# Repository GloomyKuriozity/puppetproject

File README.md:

# puppetproject
Hub for all puppet project files
ROS2 Jazzy middleware
Raspberry Pi 5/Arduino ATMega2560

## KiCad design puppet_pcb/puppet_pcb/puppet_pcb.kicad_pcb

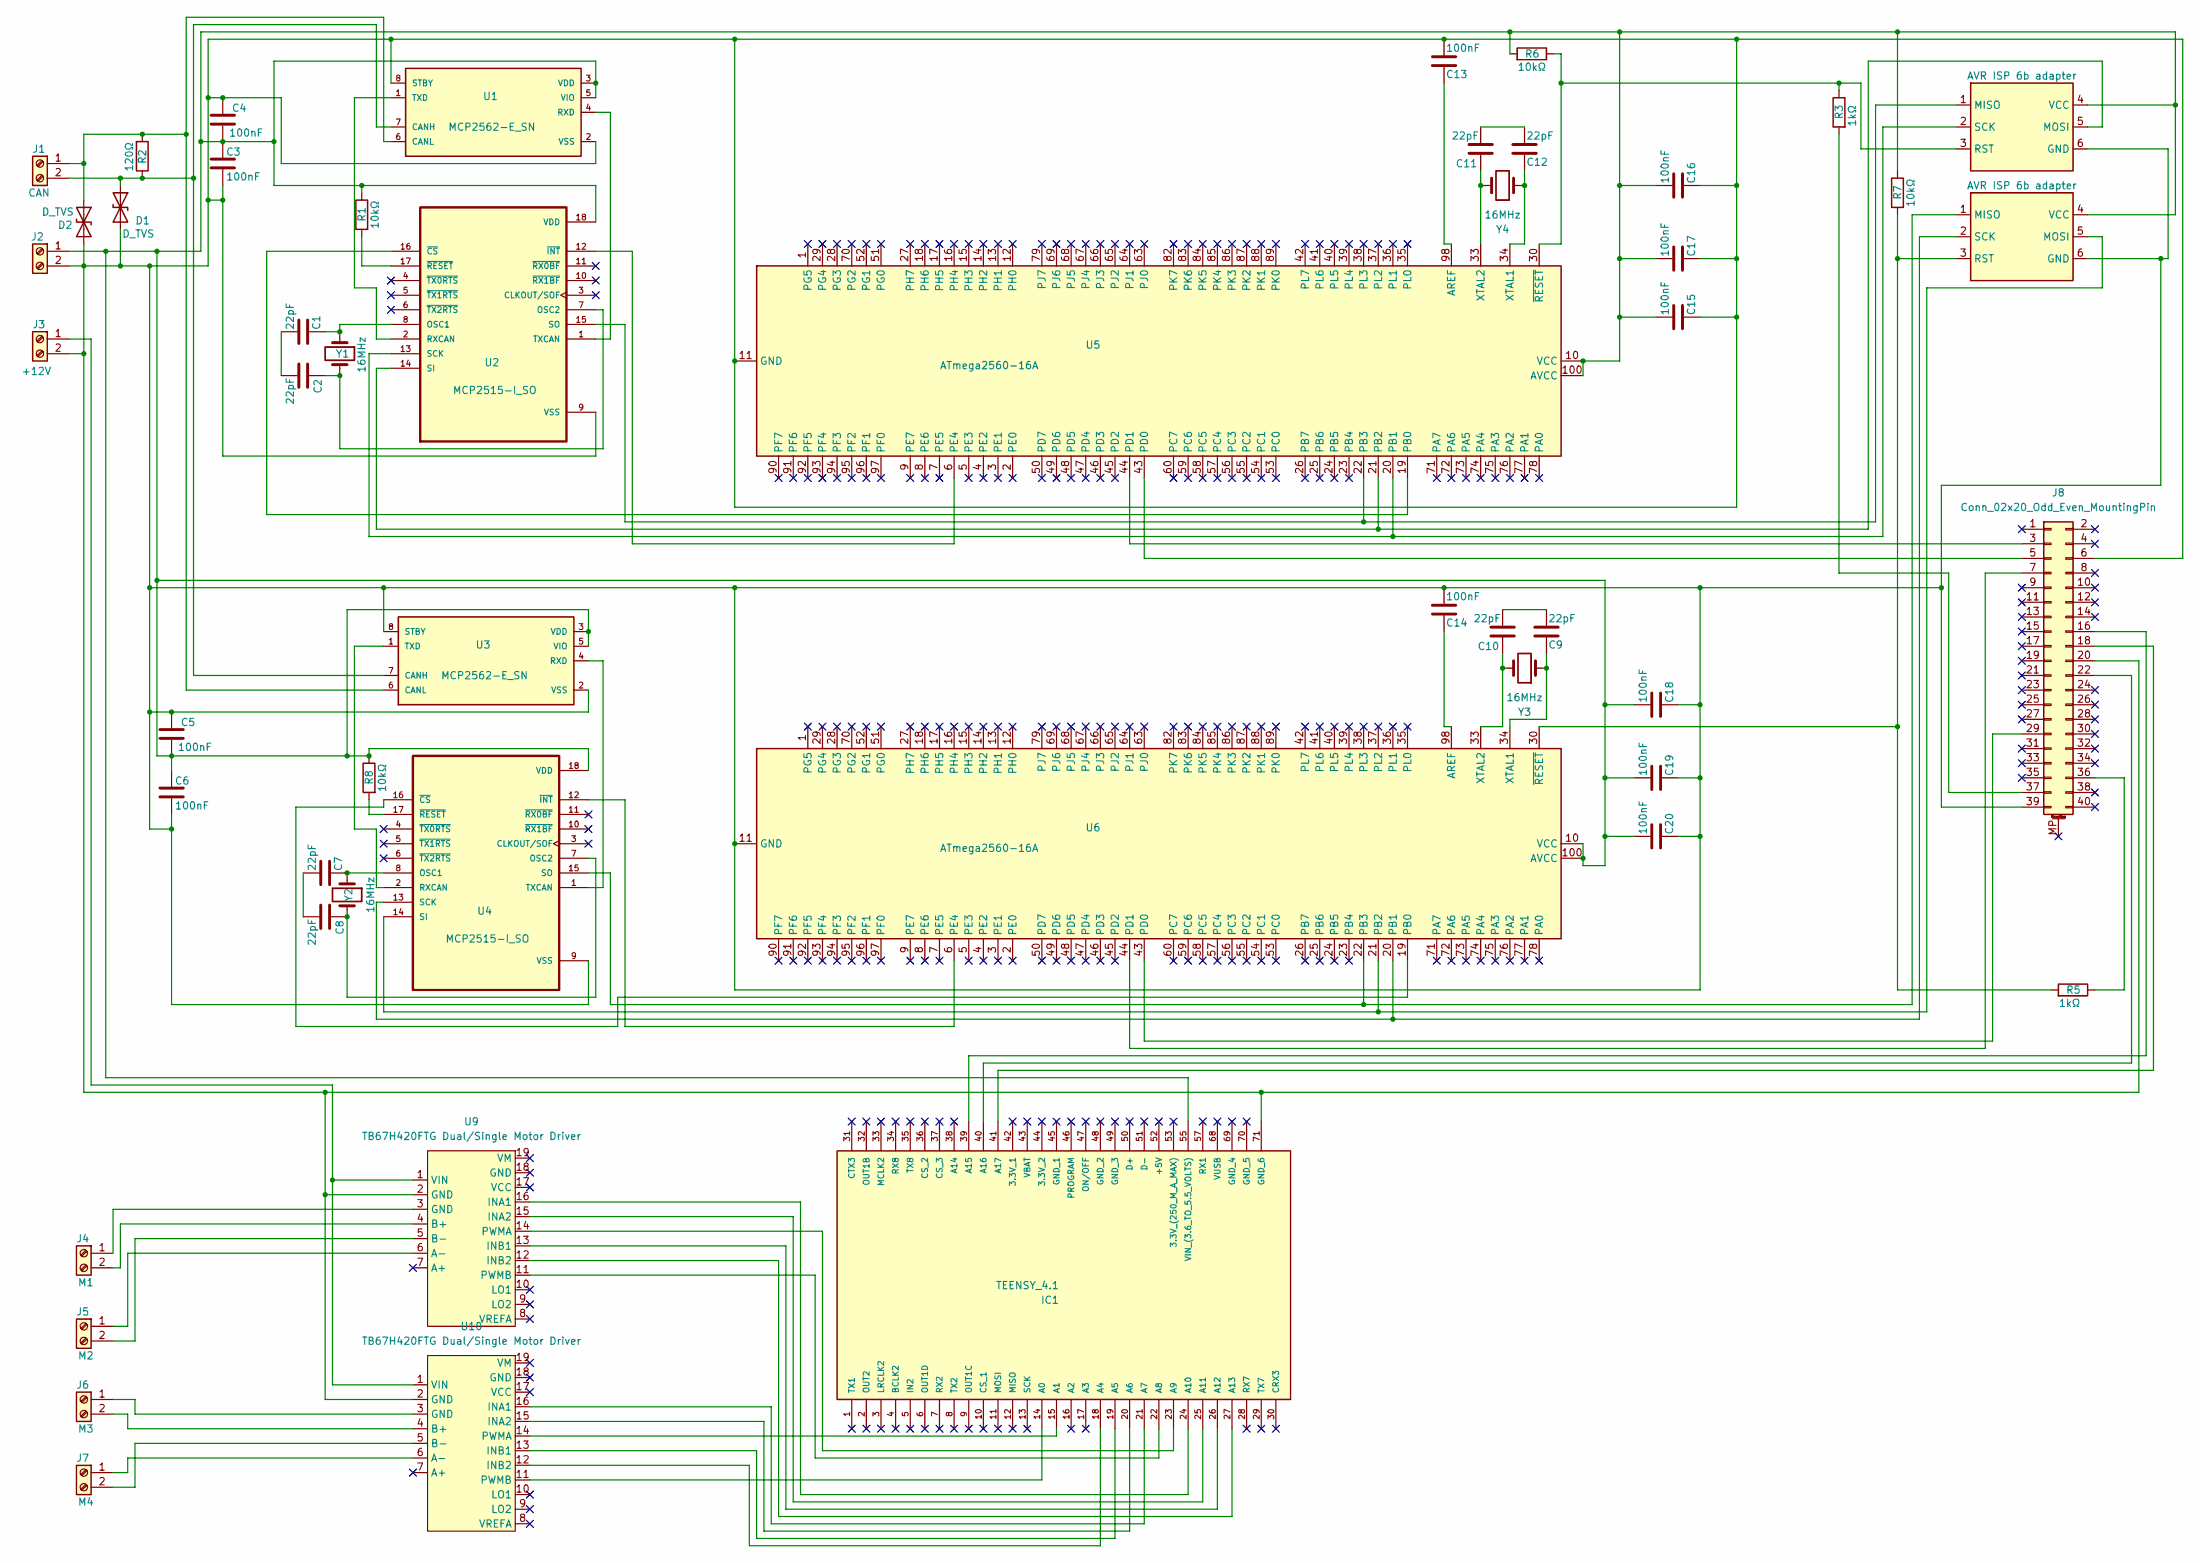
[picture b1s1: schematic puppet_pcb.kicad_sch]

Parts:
C1, C2, C7, C8, C9, C10, C11, C12: 22pF; C_0805_2012Metric
C3, C4, C5, C6, C13, C14, C15, C16, C17, C18, C19, C20: 100nF; C_0805_2012Metric
D1, D2: D_TVS; Nexperia_DSN0603-2_0.6x0.3mm_P0.4mm
IC1: TEENSY_4.1; Manufacturer_Part_Number TEENSY 4.1
J1: CAN; TerminalBlock_MaiXu_MX126-5.0-02P_1x02_P5.00mm
J2: +5V; TerminalBlock_MaiXu_MX126-5.0-02P_1x02_P5.00mm
J3: +12V; TerminalBlock_MaiXu_MX126-5.0-02P_1x02_P5.00mm
J4: M1; TerminalBlock_MaiXu_MX126-5.0-02P_1x02_P5.00mm
J5: M2; TerminalBlock_MaiXu_MX126-5.0-02P_1x02_P5.00mm
J6: M3; TerminalBlock_MaiXu_MX126-5.0-02P_1x02_P5.00mm
J7: M4; TerminalBlock_MaiXu_MX126-5.0-02P_1x02_P5.00mm
J8: Conn_02x20_Odd_Even_MountingPin; IDC-Header_2x20_P2.54mm_Vertical
R1, R6, R7, R8: 10kΩ; R_0805_2012Metric
R2: 120Ω; R_0805_2012Metric
R3, R5: 1kΩ; R_0805_2012Metric
U1, U3: MCP2562-E_SN
U2, U4: MCP2515-I_SO
U5, U6: ATmega2560-16A; TQFP-100_14x14mm_P0.5mm
U7, U8: AVR ISP 6b adapter; Adafruit 6_isp avr adapter
U9, U10: TB67H420FTG Dual/Single Motor Driver; TB67H420FTG Dual_Single Motor
Y1, Y2, Y3, Y4: 16MHz; perçant_quartz

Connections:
unnamed: C1.2, C2.2
unnamed: C7.2, C8.2
unnamed: C9.2, C10.2
unnamed: C11.2, C12.2
unnamed: D1.1 (A1), J1.2, R2.1, U1.7 (CANH), U3.7 (CANH)
unnamed: C3.2, C4.1, C5.1, C6.2, C13.2, C14.2, C15.1, C16.1, C17.1, C18.1, C19.1, C20.1, D1.2 (A2), D2.2 (A2), IC1.71 (GND_6), J2.2, J3.2, J8.6, J8.20, J8.39, U1.2 (VSS), U1.8 (STBY), U2.9 (VSS), U3.2 (VSS), U3.8 (STBY), U4.9 (VSS), U5.11 (GND), U5.32 (GND), U5.62 (GND), U5.81 (GND), U5.99 (GND), U6.11 (GND), U6.32 (GND), U6.62 (GND), U6.81 (GND), U6.99 (GND), U7.6 (GND), U8.6 (GND), U9.2 (GND), U10.2 (GND)
unnamed: D2.1 (A1), J1.1, R2.2, U1.6 (CANL), U3.6 (CANL)
unnamed: IC1.14 (A0), U10.11 (PWMB)
unnamed: IC1.15 (A1), U10.14 (PWMA)
unnamed: IC1.18 (A4), U10.12 (INB2)
unnamed: IC1.19 (A5), U10.13 (INB1)
unnamed: IC1.20 (A6), U10.15 (INA2)
unnamed: IC1.21 (A7), U10.16 (INA1)
unnamed: IC1.22 (A8), U9.11 (PWMB)
unnamed: IC1.23 (A9), U9.14 (PWMA)
unnamed: IC1.24 (A10), U9.16 (INA1)
unnamed: IC1.25 (A11), U9.15 (INA2)
unnamed: IC1.26 (A12), U9.13 (INB1)
unnamed: IC1.27 (A13), U9.12 (INB2)
unnamed: IC1.39 (A15), J8.16
unnamed: IC1.40 (A16), J8.22
unnamed: IC1.41 (A17), J8.18
unnamed: C3.1, C4.2, C5.2, C6.1, C15.2, C16.2, C17.2, C18.2, C19.2, C20.2, IC1.55 (VIN_(3.6_TO_5.5_VOLTS)), J2.1, R1.1, R6.2, R7.1, R8.1, U1.3 (VDD), U1.5 (VIO), U2.18 (VDD), U3.3 (VDD), U3.5 (VIO), U4.18 (VDD), U5.10 (VCC), U5.31 (VCC), U5.61 (VCC), U5.80 (VCC), U5.100 (AVCC), U6.10 (VCC), U6.31 (VCC), U6.61 (VCC), U6.80 (VCC), U6.100 (AVCC), U7.4 (VCC), U8.4 (VCC)
unnamed: J3.1, U9.1 (VIN), U10.1 (VIN)
unnamed: J4.1, U9.3 (GND)
unnamed: J4.2, U9.4 (B+)
unnamed: J5.1, U9.6 (A-)
unnamed: J5.2, U9.5 (B-)
unnamed: J6.1, U10.3 (GND)
unnamed: J6.2, U10.4 (B+)
unnamed: J7.1, U10.6 (A-)
unnamed: J7.2, U10.5 (B-)
unnamed: J8.3, U5.44 (PD1)
unnamed: J8.5, U5.43 (PD0)
unnamed: J8.7, U6.44 (PD1)
unnamed: J8.29, U6.43 (PD0)
unnamed: J8.36, R5.1
unnamed: J8.37, R3.2
unnamed: U1.4 (RXD), U2.1 (TXCAN)
unnamed: U1.1 (TXD), U2.2 (RXCAN)
unnamed: C1.1, U2.8 (OSC1), Y1.1
unnamed: C2.1, U2.7 (OSC2), Y1.2
unnamed: U2.13 (SCK), U5.20 (PB1), U7.2 (SCK)
unnamed: U2.14 (SI), U5.21 (PB2), U7.5 (MOSI)
unnamed: U2.15 (SO), U5.22 (PB3), U7.1 (MISO)
unnamed: U2.16 (~CS), U5.19 (PB0)
unnamed: U2.12 (~INT), U5.6 (PE4)
unnamed: R1.2, U2.17 (~RESET)
unnamed: U3.4 (RXD), U4.1 (TXCAN)
unnamed: U3.1 (TXD), U4.2 (RXCAN)
unnamed: C7.1, U4.8 (OSC1), Y2.1
unnamed: C8.1, U4.7 (OSC2), Y2.2
unnamed: U4.13 (SCK), U6.20 (PB1), U8.2 (SCK)
unnamed: U4.14 (SI), U6.21 (PB2), U8.5 (MOSI)
unnamed: U4.15 (SO), U6.22 (PB3), U8.1 (MISO)
unnamed: U4.16 (~CS), U6.19 (PB0)
unnamed: U4.12 (~INT), U6.6 (PE4)
unnamed: R8.2, U4.17 (~RESET)
unnamed: C13.1, U5.98 (AREF)
unnamed: C12.1, U5.34 (XTAL1), Y4.1
unnamed: C11.1, U5.33 (XTAL2), Y4.2
unnamed: R3.1, R6.1, U5.30 (~RESET), U7.3 (RST)
unnamed: C14.1, U6.98 (AREF)
unnamed: C9.1, U6.34 (XTAL1), Y3.1
unnamed: C10.1, U6.33 (XTAL2), Y3.2
unnamed: R5.2, R7.2, U6.30 (~RESET), U8.3 (RST)

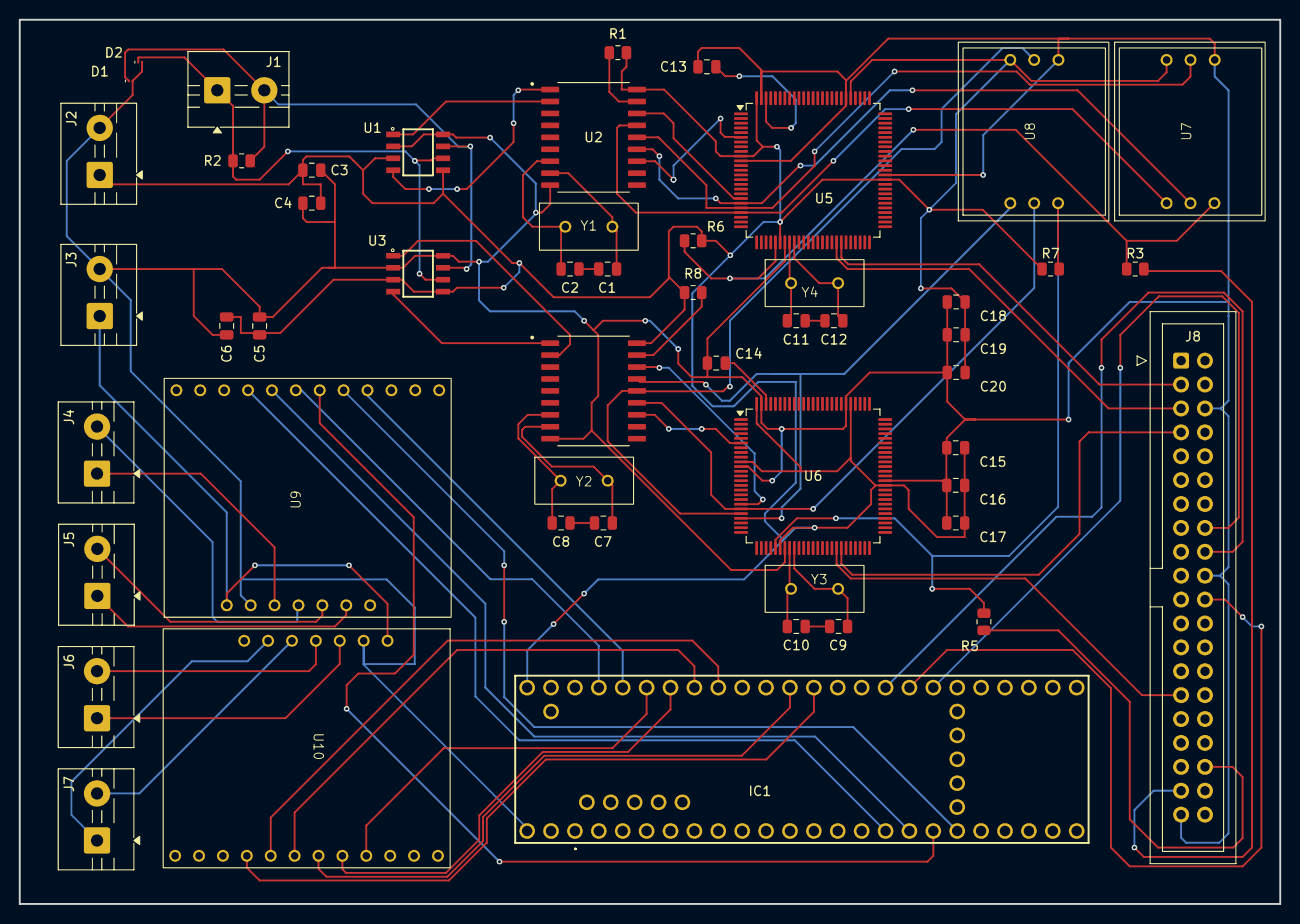
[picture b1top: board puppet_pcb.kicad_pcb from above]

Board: 2 copper layers, 134.0 x 94.0 mm, 52 parts (0 on the bottom side), 66 nets.

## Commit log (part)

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2025-06-04 Add app_command_pkg
    Everything related to communication brain/robot
2025-06-04 Add explore_lite
    Made for Gazebo (ROS2 Jazzy version) explore lite algorithm test
2025-06-04 Add explore_lite_IRL
    Conversion from explore lite for Gazebo to IRL tests
2025-06-04 Add puppet_irl_bringup
    slam_toolbox IRL usage package
2025-06-04 Add robot_control
    Communication with the robot, and conversion of data
2025-06-04 Add scan_from_lidar package
    Manage 2D lidar
2025-06-04 code_workspace
    Arduino and test scripts
2025-06-13 Update nav2_params.yaml
    Changed inflation radius costmaps
2025-06-13 Update nav2_launch.py
    Comment out map server and amcl
2025-06-13 Rotation Shim Controller for Reverse Driving
2025-12-03 Add GPIO control for UP/DOWN commands
    Updated last modification date and added GPIO control for UP/DOWN commands.
2025-12-04 Refactor GPIO state management with gpioset
    Refactor GPIO handling to use gpioset commands instead of RPi.GPIO library, allowing for better compatibility and control.
2025-12-04 Refactor GPIO control logic in app_command.py
    Removed GPIO setup and cleanup code for UP/DOWN control.
2025-12-04 Implement STOP_PROBE command handling
    Added handling for STOP_PROBE command to stop probe motion.
2025-12-05 Refactor home_sequence function indentation
2025-12-05 Improve GPIO command handling with error logging
    Refactor GPIO command execution to capture output and handle errors.
2025-12-06 Refactor GPIO state setting logic
2025-12-08 Add contamination subscription and handling
2025-12-08 Update contamination topic to 'sfp100/contamination'
2025-12-08 Add Float32MultiArray import to app_command.py
2025-12-08 Change contamination subscription to Float32MultiArray
    Updated contamination subscription and handling to use Float32MultiArray instead of Float32. Adjusted value extraction to take the first element of the array.
2025-12-08 Refactor on_contamination to send specific value
    Update contamination handling to send beta_gamma_bq_cm2 value.
2026-03-02 Latest versions
2026-03-02 organize
2026-03-04 new updates
2026-03-30 Update app_command.py
    on contamination data sent to app when connected
2026-03-30 changes to arduino and rp
    - Odom ino code has been improved with battery voltage parsing
    - robot_control retreive battery info and translate it in robot_info topic
2026-03-30 add battery info sent to app
2026-03-31 a lot for nothing
2026-04-01 Refactor I2C read and odometry processing
    Updated I2C reading method and improved odometry handling.
2026-04-01 Refactor battery voltage handling and telemetry updates
2026-04-01 mapping started + battery/robot info retreived
2026-04-02 Mapping stop
2026-04-07 Mapping finally op
2026-04-09 Changes in mapping and control
    - Send map and pose to app
    - change launch in manual mapping
    - cmd_vel thread out, less memory
    - clean up robot_control, app_command
2026-04-10 record map in map library
2026-04-14 update resolution
2026-06-22 Fix cartography drop out
2026-06-22 PCB kicad
2026-06-26 pcb done
2026-06-28 tests heatmap creator
2026-06-30 pcb changes
